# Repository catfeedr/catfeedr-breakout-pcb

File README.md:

# catfeedr-breakout-pcb
PCB breakout board for catfeedr

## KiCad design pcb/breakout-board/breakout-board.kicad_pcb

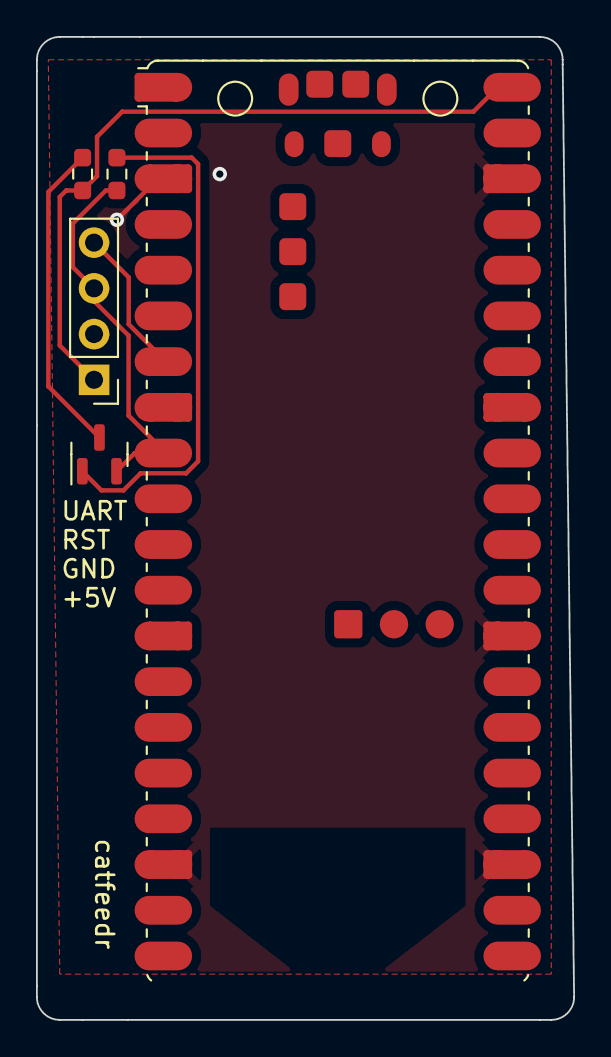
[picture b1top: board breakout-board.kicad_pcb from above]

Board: 2 copper layers, 29.8 x 54.6 mm, 5 parts (0 on the bottom side), 6 nets.

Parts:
J1: WL-134 RF Module; PinHeader_1x04_P2.54mm_Vertical
Q1: BSS138; SOT-23
R1, R2: 10k; R_0603_1608Metric_Pad0.98x0.95mm_HandSolder
U1: Pico; RaspberryPi_Pico_W_SMD

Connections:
+3V3: Q1.1 (G), R1.1
+5V: J1.1, R2.1, U1.40 (VBUS)
/RST_3V3: J1.3, Q1.2 (S), R1.2, U1.9 (GPIO6)
/UART1_RX: J1.4, U1.7 (GPIO5)
/WL-134-RF-Module/RST(+5V): Q1.3 (D), R2.2
GND: J1.2, U1.3 (GND), U1.8 (GND), U1.18 (GND), U1.23 (GND), U1.28 (GND), U1.38 (GND)

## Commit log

2023-12-08 First WIP version of breakout board
